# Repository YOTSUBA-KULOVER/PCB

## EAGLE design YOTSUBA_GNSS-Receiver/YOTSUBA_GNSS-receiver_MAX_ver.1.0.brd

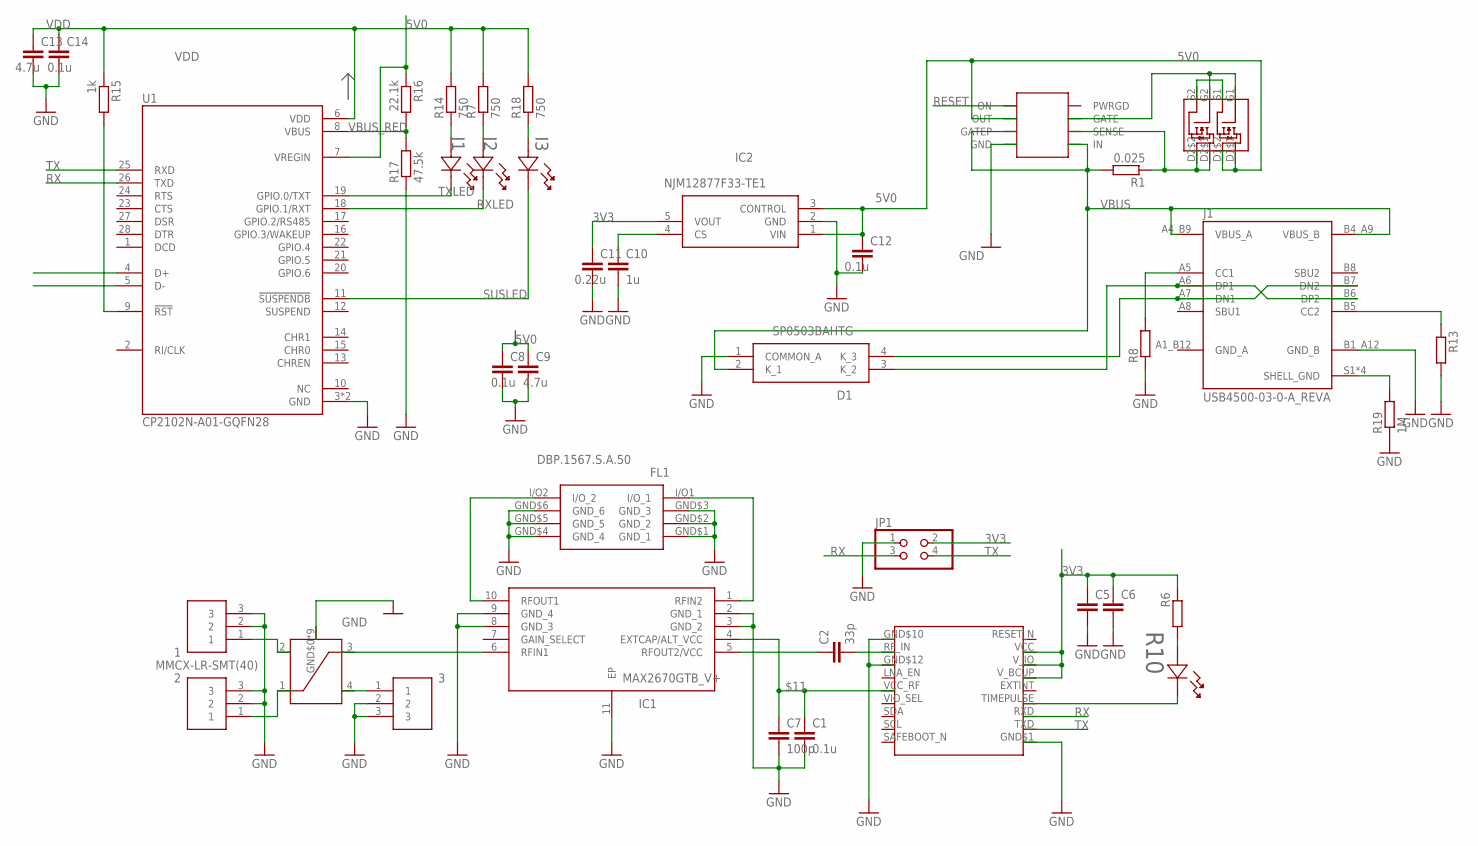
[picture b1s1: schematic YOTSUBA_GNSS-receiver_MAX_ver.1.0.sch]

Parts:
1, 2, 3: MMCX-LR-SMT(40)
C1, C8, C12, C14: 0.1u; C1608
C2: 33p; C1608
C5, C6: C-EUC1608; C1608
C7: 100p; C1608
C9, C13: 4.7u; C1608
C10: 1u; C1608
C11: 0.22u; C1608
D1: SP0503BAHTG
FL1: DBP.1567.S.A.50; DBP1567SA50
I1, I2, I3: SML-E12P8WT86; LED_SMLD12_ROM
IC1: MAX2670GTB_V+; SON50P300X300X80-11N
IC2: NJM12877F33-TE1; SOT95P280X120-5N
J1: USB4500-03-0-A_REVA; GCT_USB4500-03-0-A_REVA
JP1: PINHD-2X2; 2X02
R1: 0.025; R0603
R6, R8, R13: R-EU_R0603; R0603
R7, R14, R18: 750; R0603
R10: SML-E12P8WT86; LED_SMLD12_ROM
R15: 1k; R0603
R16: 22.1k; R0603
R17: 47.5k; R0603
R19: 1M; R0603
U1: CP2102N-A01-GQFN28; QFN50P500X500X80-29N
U$1: MAX_M10S; MAX-M10S
U$3: HC125.A
U$7: DMG6898LSD; SOIC127P600X150-8N
U$8: LTC4361; SOP65P280X100-8N

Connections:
3V3: C5.1, C6.1, C11.1, IC2.5 (VOUT), JP1.2, R6.2, U$1.VCC, U$1.V_BCUP (V_BCKP), U$1.V_IO
5V0: C8.1, C9.1, C12.1, IC2.1 (VIN), IC2.3 (CONTROL), R16.1, U1.7 (VREGIN), U$7.D1$1, U$7.D1$2, U$8.OUT
$11: C1.1, C7.1, IC1.4 (EXTCAP/ALT_VCC), U$1.VCC_RF
D+: D1.3 (K_2), J1.A6 (DP1), J1.B6 (DP2), U1.4 (D+)
D-: D1.4 (K_3), J1.A7 (DN1), J1.B7 (DN2), U1.5 (D-)
GND: 1.2, 1.3, 2.2, 2.3, 3.2, 3.3, C1.2, C5.2, C6.2, C7.2, C8.2, C9.2, C10.2, C11.2, C12.2, C13.2, C14.2, D1.1 (COMMON_A), FL1.GND$1 (GND_1), FL1.GND$2 (GND_2), FL1.GND$3 (GND_3), FL1.GND$4 (GND_4), FL1.GND$5 (GND_5), FL1.GND$6 (GND_6), IC1.2 (GND_1), IC1.3 (GND_2), IC1.8 (GND_3), IC1.9 (GND_4), IC1.11 (EP), IC2.2 (GND), J1.A1_B12 (GND_A), J1.B1_A12 (GND_B), JP1.1, R8.1, R13.2, R17.1, R19.1, U1.3 (GND), U1.29 (GND), U$1.GND$1, U$1.GND$10, U$1.GND$12, U$3.GND$0 (GND), U$3.GND$1 (GND), U$3.GND$2 (GND), U$3.GND$3 (GND), U$3.GND$4 (GND), U$3.GND$5 (GND), U$3.GND$6 (GND), U$3.GND$7 (GND), U$3.GND$8 (GND), U$8.GND
unnamed: 1.1, U$3.2
unnamed: 2.1, U$3.1
unnamed: IC1.6 (RFIN1), U$3.3
unnamed: C10.1, IC2.4 (CS)
unnamed: I2.2, R7.1
unnamed: 3.1, U$3.4
unnamed: FL1.I/O2 (I/O_2), IC1.10 (RFOUT1)
unnamed: FL1.I/O1 (I/O_1), IC1.1 (RFIN2)
unnamed: C2.1, IC1.5 (RFOUT2/VCC)
unnamed: C2.2, U$1.RF_IN
unnamed: I1.2, R14.1
unnamed: R10.1, U$1.TIMEPULSE
unnamed: R6.1, R10.2
unnamed: I3.2, R18.1
unnamed: U$7.S1, U$7.S2
unnamed: R1.1, U$7.D2$1, U$7.D2$2, U$8.SENSE
unnamed: J1.B5 (CC2), R13.1
unnamed: U$7.G1, U$7.G2, U$8.GATE
unnamed: J1.A5 (CC1), R8.2
unnamed: J1.S1 (SHELL_GND), J1.S2 (SHELL_GND), J1.S3 (SHELL_GND), J1.S4 (SHELL_GND), R19.2
unnamed: R15.2, U1.9 (!RST)
RESET: U$8.ON
RX: JP1.3, U1.26 (TXD), U$1.RXD
RXLED: I2.1, U1.18 (GPIO.1/RXT)
SUSLED: I3.1, U1.11 (!SUSPENDB)
TX: JP1.4, U1.25 (RXD), U$1.TXD
TXLED: I1.1, U1.19 (GPIO.0/TXT)
VBUS: D1.2 (K_1), J1.A4_B9 (VBUS_A), J1.B4_A9 (VBUS_B), R1.2, U$8.GATEP, U$8.IN
VBUS_RED: R16.2, R17.2, U1.8 (VBUS)
VDD: C13.1, C14.1, R7.2, R14.2, R15.1, R18.2, U1.6 (VDD)

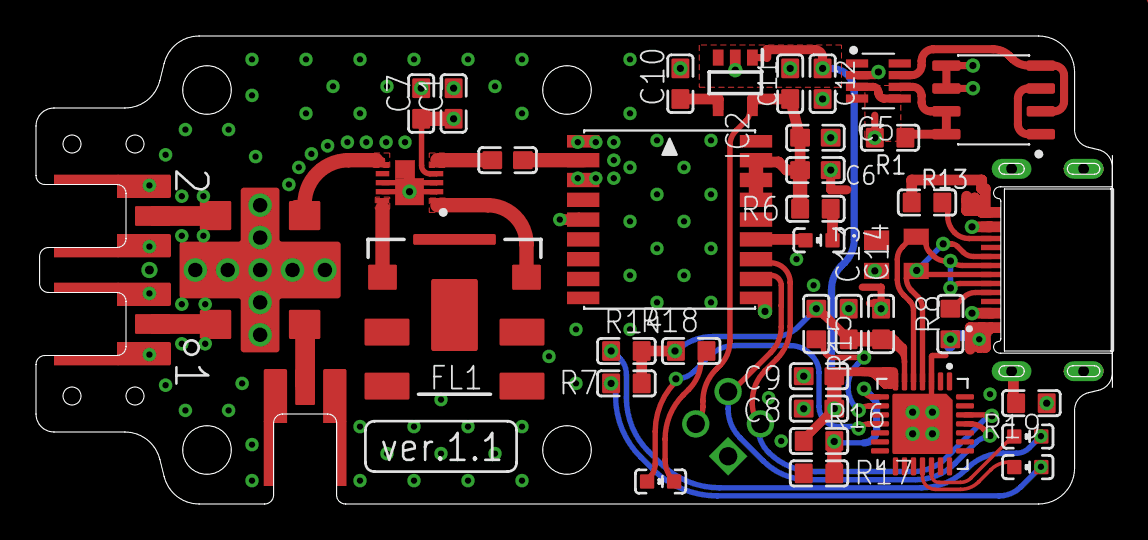
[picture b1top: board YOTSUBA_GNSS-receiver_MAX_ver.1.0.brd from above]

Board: 2 copper layers, 59.8 x 26.0 mm, 41 parts (0 on the bottom side), 35 nets.

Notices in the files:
parts and their libraries:
COPYRIGHT: Copyright (C) 2023 Ultra Librarian. All rights reserved.
